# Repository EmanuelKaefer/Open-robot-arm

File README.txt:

# Robot Arm Project

This repository contains an ongoing project focused on the development of a 6-DOF robotic arm. The project is part of a school project and may later be extended into a larger final thesis project. The goal is to design and build a functional robotic arm while gaining experience in mechanical design, electronics, embedded systems, and software.

The repository includes hardware designs, firmware, control software, and documentation. As the project progresses, new features, improvements, and design iterations will be added.

# Technical Details
* Mechanical: Largely custom built. Most components are designed specifically for this project and manufactured using 3D printing.
* Electronics: Custom designed PCB created in KiCad, utilizing an STM32F446RET6 chip and TMC5160t pro 1.0 motor drivers.
* Software: Control algorithms are developed using MATLAB for modeling, simulation, and deployment.

# Licensing
This project is dual-licensed to respect the different requirements of hardware and software development:

* Software: All code within this repository is licensed under the GNU General Public License v3.0 (GPL-3.0). See `LICENSE-SOFTWARE` for details.
* Hardware: All hardware designs, including PCB layouts and mechanical CAD files, are licensed under the CERN Open Hardware Licence Version 2 (CERN-OHL-S-2.0). See `LICENSE-HARDWARE` for details.

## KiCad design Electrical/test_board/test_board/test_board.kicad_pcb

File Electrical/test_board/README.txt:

# Test Board

This board will test the motor drivers and SPI communication before actually implementing them on the driver board.

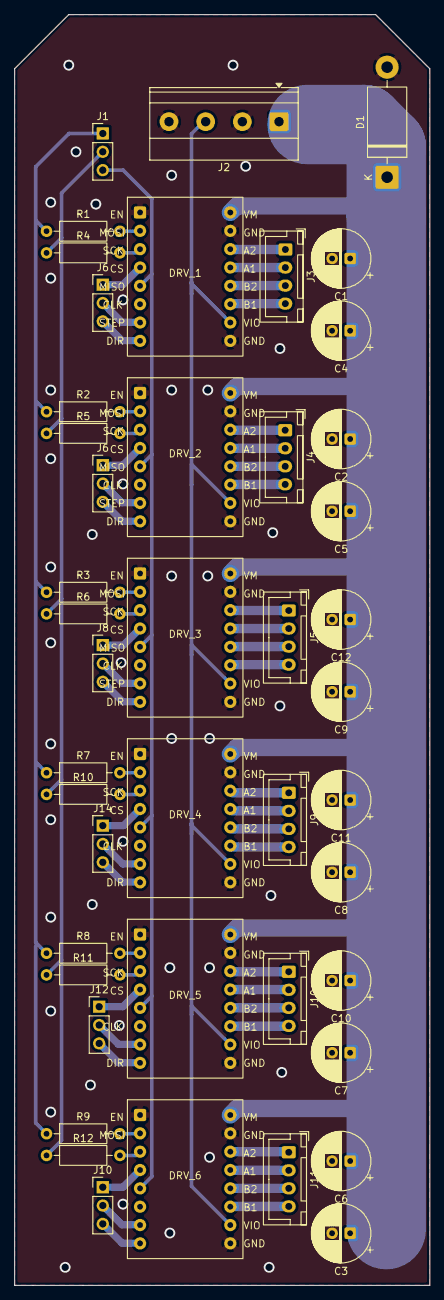
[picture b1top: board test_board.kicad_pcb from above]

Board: 2 copper layers, 57.5 x 176.0 mm, 45 parts (0 on the bottom side), 60 nets.

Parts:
C1, C2, C3, C7, C8, C9: 100nF; CP_Radial_D8.0mm_P2.50mm
C4, C5, C6, C10, C11, C12: 100uF; CP_Radial_D8.0mm_P2.50mm
D1: D_TVS; D_DO-201AD_P15.24mm_Horizontal
DRV_1, DRV_2, DRV_3, DRV_4, DRV_5, DRV_6: TMC5160T_V1.0; TMC5160T_Pro_V1.0_Breakout
J1, J6, J6#2, J8, J10, J12, J14: Conn_01x03_Pin; PinHeader_1x03_P2.54mm_Vertical
J2: Screw_Terminal_01x04; TerminalBlock_Phoenix_MKDS-1,5-4-5.08_1x04_P5.08mm_Horizont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
J3, J4, J5, J9, J10#2, J11: Conn_01x04_Socket; JST_XH_B4B-XH-A_1x04_P2.50mm_Vertical
R1, R2, R3, R4, R5, R6, R7, R8, R9, R10, R11, R12: 0Ohm; R_Axial_DIN0207_L6.3mm_D2.5mm_P10.16mm_Horizontal

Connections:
+3.3V: DRV_1.14, DRV_2.14, DRV_3.14, DRV_4.14, DRV_5.14, DRV_6.14, J2.3
+24V: C1.1, C2.1, C3.1, C4.1, C5.1, C6.1, C7.1, C8.1, C9.1, C10.1, C11.1, C12.1, D1.1 (A1), DRV_1.2, DRV_2.2, DRV_3.2, DRV_4.2, DRV_5.2, DRV_6.2, J2.1
GND: C1.2, C2.2, C3.2, C4.2, C5.2, C6.2, C7.2, C8.2, C9.2, C10.2, C11.2, C12.2, D1.2 (A2), DRV_1.1, DRV_1.4, DRV_1.16, DRV_2.1, DRV_2.4, DRV_2.16, DRV_3.1, DRV_3.4, DRV_3.16, DRV_4.1, DRV_4.4, DRV_4.16, DRV_5.1, DRV_5.4, DRV_5.16, DRV_6.1, DRV_6.4, DRV_6.16, J2.2, J2.4
MISO: DRV_1.9, DRV_2.9, DRV_3.9, DRV_4.9, DRV_5.9, DRV_6.9, J1.3
MOSI: J1.1, R1.1, R2.1, R3.1, R7.1, R8.1, R9.1
unnamed: DRV_1.3, R1.2
unnamed: DRV_1.5, R4.2
unnamed: DRV_1.6, J3.1
unnamed: DRV_1.7, J6.1
unnamed: DRV_1.8, J3.2
unnamed: DRV_1.10, J3.3
unnamed: DRV_1.12, J3.4
unnamed: DRV_1.13, J6.2
unnamed: DRV_1.15, J6.3
unnamed: DRV_2.3, R2.2
unnamed: DRV_2.5, R5.2
unnamed: DRV_2.6, J4.1
unnamed: DRV_2.7, J6#2.1
unnamed: DRV_2.8, J4.2
unnamed: DRV_2.10, J4.3
unnamed: DRV_2.12, J4.4
unnamed: DRV_2.13, J6#2.2
unnamed: DRV_2.15, J6#2.3
unnamed: DRV_3.3, R3.2
unnamed: DRV_3.5, R6.2
unnamed: DRV_3.6, J5.1
unnamed: DRV_3.7, J8.1
unnamed: DRV_3.8, J5.2
unnamed: DRV_3.10, J5.3
unnamed: DRV_3.12, J5.4
unnamed: DRV_3.13, J8.2
unnamed: DRV_3.15, J8.3
unnamed: DRV_4.3, R7.2
unnamed: DRV_4.5, R10.2
unnamed: DRV_4.6, J9.1
unnamed: DRV_4.7, J14.1
unnamed: DRV_4.8, J9.2
unnamed: DRV_4.10, J9.3
unnamed: DRV_4.12, J9.4
unnamed: DRV_4.13, J14.2
unnamed: DRV_4.15, J14.3
unnamed: DRV_5.3, R8.2
unnamed: DRV_5.5, R11.2
unnamed: DRV_5.6, J10#2.1
unnamed: DRV_5.7, J12.1
unnamed: DRV_5.8, J10#2.2
unnamed: DRV_5.10, J10#2.3
unnamed: DRV_5.12, J10#2.4
unnamed: DRV_5.13, J12.2
unnamed: DRV_5.15, J12.3
unnamed: DRV_6.3, R9.2
unnamed: DRV_6.5, R12.2
unnamed: DRV_6.6, J11.1
unnamed: DRV_6.7, J10.1
unnamed: DRV_6.8, J11.2
unnamed: DRV_6.10, J11.3
unnamed: DRV_6.12, J11.4
unnamed: DRV_6.13, J10.2
unnamed: DRV_6.15, J10.3
SCK: J1.2, R4.1, R5.1, R6.1, R10.1, R11.1, R12.1

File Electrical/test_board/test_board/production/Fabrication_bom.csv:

Designator,Footprint,Quantity,Value,LCSC Part #
"C1, C2, C3, C7, C8, C9",CP_Radial_D8.0mm_P2.50mm,6,100nF,
"C10, C11, C12, C4, C5, C6",CP_Radial_D8.0mm_P2.50mm,6,100uF,
D1,D_DO-201AD_P15.24mm_Horizontal,1,D_TVS,
"DRV_1, DRV_2, DRV_3, DRV_4, DRV_5, DRV_6",TMC5160T_Pro_V1.0_Breakout,6,TMC5160T_V1.0,
"J1, J10_2, J12, J14, J6_2, J6, J8",PinHeader_1x03_P2.54mm_Vertical,7,Conn_01x03_Pin,
"J10, J11, J3, J4, J5, J9",JST_XH_B4B-XH-A_1x04_P2.50mm_Vertical,6,Conn_01x04_Socket,
J2,"TerminalBlock_Phoenix_MKDS-1,5-4-5.08_1x04_P5.08mm_Horizontal",1,Screw_Terminal_01x04,
"R1, R10, R11, R12, R2, R3, R4, R5, R6, R7, R8, R9",R_Axial_DIN0207_L6.3mm_D2.5mm_P10.16mm_Horizontal,12,0Ohm,

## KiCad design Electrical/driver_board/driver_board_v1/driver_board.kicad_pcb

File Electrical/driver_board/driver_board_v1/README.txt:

# Motor Driver Board

This board will handle the power and control signals for the robot arm's motors.

Decisions pending:
- Supply voltage (12V/24V/etc)
- Motor driver ICs
- MCU interface logic levels
- Connector types
- Current limits

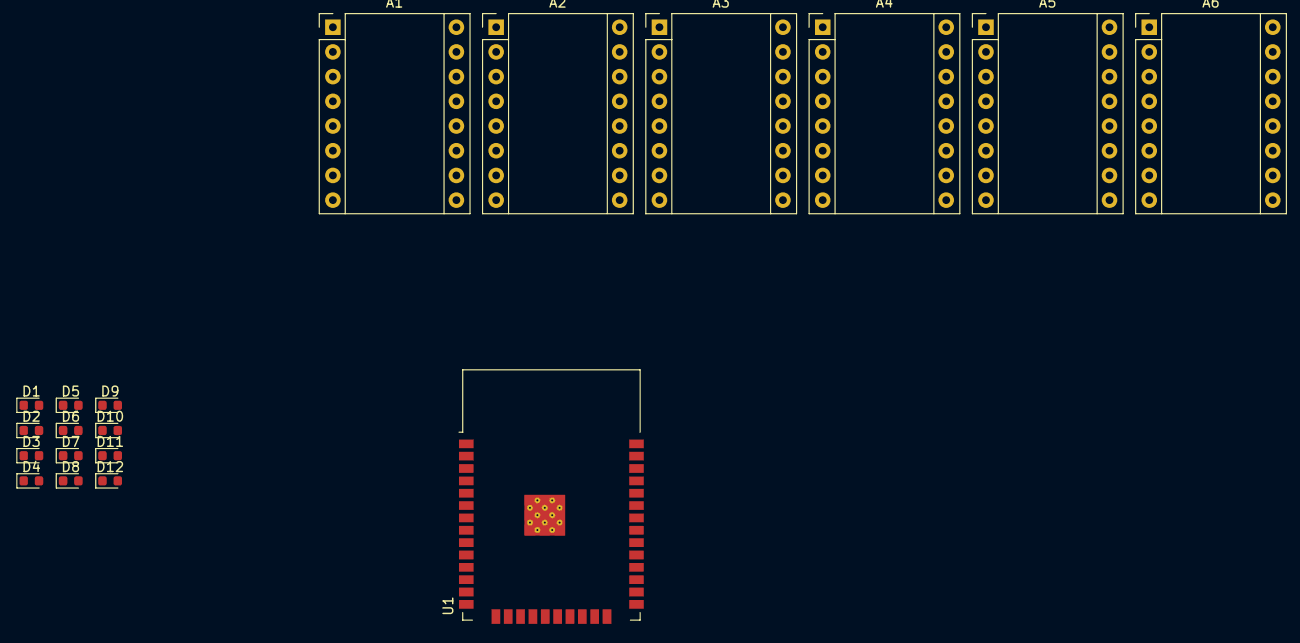
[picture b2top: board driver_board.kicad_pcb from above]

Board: 2 copper layers, 19 parts (0 on the bottom side), 26 nets, no tracks yet.

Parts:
A1, A2, A3, A4, A5, A6: Pololu_Breakout_A4988; Pololu_Breakout-16_15.2x20.3mm
D1, D2, D3, D4, D5, D6, D7, D8, D9, D10, D11, D12: LED; LED_0603_1608Metric
U1: ESP32-WROOM-32

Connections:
GND: A1.9 (~ENABLE), A2.9 (~ENABLE), A3.9 (~ENABLE), A4.9 (~ENABLE), A5.9 (~ENABLE), A6.9 (~ENABLE)
IO2: A6.13 (~RESET), U1.24 (IO2)
IO4: A5.13 (~RESET), U1.26 (IO4)
IO5: A4.13 (~RESET), U1.29 (IO5)
IO12: A3.13 (~RESET), U1.14 (IO12)
IO13: A2.13 (~RESET), U1.16 (IO13)
IO14: A1.13 (~RESET), U1.13 (IO14)
IO33: A1.10 (MS1), A2.10 (MS1), A3.10 (MS1), A4.10 (MS1), A5.10 (MS1), A6.10 (MS1)
IO34: A1.11 (MS2), A2.11 (MS2), A3.11 (MS2), A4.11 (MS2), A5.11 (MS2), A6.11 (MS2)
IO35: A1.12 (MS3), A2.12 (MS3), A3.12 (MS3), A4.12 (MS3), A5.12 (MS3), A6.12 (MS3)
NC: U1.3 (EN), U1.4 (SENSOR_VP), U1.5 (SENSOR_VN), U1.17 (SHD/SD2), U1.18 (SWP/SD3), U1.19 (SCS/CMD), U1.20 (SCK/CLK), U1.21 (SDO/SD0), U1.22 (SDI/SD1), U1.25 (IO0)
unnamed: A1.16 (DIR), D2.1 (K)
unnamed: A1.15 (STEP), D1.1 (K)
unnamed: A1.2 (VDD), A1.14 (~SLEEP), A2.2 (VDD), A2.14 (~SLEEP), A3.2 (VDD), A3.14 (~SLEEP), A4.2 (VDD), A4.14 (~SLEEP), A5.2 (VDD), A5.14 (~SLEEP), A6.2 (VDD), A6.14 (~SLEEP), U1.2 (VDD)
unnamed: A1.8 (VMOT), A2.8 (VMOT), A3.8 (VMOT), A4.8 (VMOT), A5.8 (VMOT), A6.8 (VMOT)
unnamed: A2.16 (DIR), D8.1 (K)
unnamed: A2.15 (STEP), D7.1 (K)
unnamed: A3.16 (DIR), D4.1 (K)
unnamed: A3.15 (STEP), D3.1 (K)
unnamed: A4.16 (DIR), D10.1 (K)
unnamed: A4.15 (STEP), D9.1 (K)
unnamed: A5.16 (DIR), D6.1 (K)
unnamed: A5.15 (STEP), D5.1 (K)
unnamed: A6.16 (DIR), D12.1 (K)
unnamed: A6.15 (STEP), D11.1 (K)
unnamed: A1.1 (GND), A1.7 (GND), A2.1 (GND), A2.7 (GND), A3.1 (GND), A3.7 (GND), A4.1 (GND), A4.7 (GND), A5.1 (GND), A5.7 (GND), A6.1 (GND), A6.7 (GND), U1.1 (GND), U1.15 (GND), U1.38 (GND), U1.39 (GND)

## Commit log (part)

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2025-10-09 Test
    Test
2025-10-09 Repository Structure
    Added Folders
2025-10-10 Mechanical parts prototype
    Prototype for the Arm
2025-10-11 V2 Prototype
2025-10-12 KiCad project and README for motor driver board
2025-10-12 Initial software skeleton and README for robot arm control
2025-10-12 Initial README for the project
2025-10-12 Smaller clearance
2025-10-12 added parts
2025-10-13 V3 1st joint spun by nema 17
    Base motor added spins 1st joint
2025-10-14 Driver_Board schematic changes
    Added smoothing capacitors
2025-10-14 Update to driver board v1
2025-10-14 Updated driver board v1
    New dip switch allignment and assigned first footprints
2025-10-15 V3 new design
2025-10-15 V3_3 Forearm assembly added
2025-10-17 Gearing added
2025-10-19 Cover added to oberarm
2025-10-19 small tweaks
2025-11-04 Create Endschalter1.ino
    first test code
2025-11-05 small changes
    some changes were made
2025-11-05 fore arm steuerrung mit homing funktion
2025-11-05 manual reset
    reset per vor und zurück
2025-11-06 Design changes
2025-11-06 new code + small design changes
    new code for oberarm + fore-oberarm together and small design tweaks
2025-11-07 software tweaks
2025-11-07 Base plate and gears added
2025-11-10 added new gears
2025-11-12 Updates to MCU
2025-11-13 urdf
2025-11-13 New urdf + mesh
2025-11-13 Update to mcu
2025-11-13 ros2 first prototype
2025-11-13 small tweaks in the urdf
2025-11-19 changes to make rivz worh
    Changes in the urdf and meshes to make rivz show the current arm Version
2025-11-23 V4 Robotarm design added
2025-11-24 manual controller changes
2025-11-24 mostly finished V4 arm
2025-11-25 urdf + collisions added
2025-11-25 name changes
2025-11-26 V4 base added
2025-11-26 3mfs of V4 added
2025-12-01 change of file structure
2025-12-02 gripper v1 and v2 added
2025-12-02 gripper added to robotarm
2025-12-04 Full gripper, universal gripper and urdf added
    Full gripper, universal gripper and urdf for self made gripper added
2025-12-04 removed old files
2026-01-13 Repository clean up
2026-02-02 initial commit
    adds urdf, csv, meshes and a simple Matlab script which displays the robot
2026-02-02 Update MATLAB live script show_robot.mlx
    Update the show_robot.mlx MATLAB live script used for the robot arm visualization. It now displays a few important parameters of the robot
2026-02-04 very simple algorithm ik and first simulink try
    A very simple Matbal inverse kinematics algorithm and a first simulink programm which only displays the robot
2026-02-05 Update to circuit
2026-02-05 Added pin definition
2026-02-05 first try in motion planing and ik in Simulink
    a matlab script for simple waypoint motion planing in matlab and a ik solver and simulation in simulink
2026-02-16 first try in adding pick-and-place motion planning with IK and trajectory generation
    feat: first try in adding pick-and-place motion planning with IK and trajectory generation
    - Connect Transform Trajectory to Inverse Kinematics block
    - Add Simulink-PS Converter input filtering (order 2) for smooth joint motion
    - Add Unit Delay feedback for IK initial guess continuity
    - Add model InitFcn callback to auto-load robot model
2026-02-17 add pick-and-place trajectory planning with multi-waypoint support
    Add Trapezoidal Velocity Profile Trajectory block for smooth
    multi-waypoint path generation (replaces chained Transform Trajectory)
    Tested with 4 waypoints for pick-lift-move-place cycle
    Without any gripper support yet
2026-02-19 first try in making a gripper controller
    added more waypoints for a better pick and place operation and fixed position of pick and place objekt.
    first steps in creating a gripper controller.
2026-02-26 small changes
2026-03-02 small changes and clean up
    deleted gripper controller
2026-03-04 first steps in making the simulink model ready to generate code for a microprozessor
    first steps in making the simulink model ready to generate code for a microprozessor
    removed the inverse kinematiks block in the simulink model and changed the waypoints from cartesian to joint angles
2026-03-06 Added full PSU architecture to driverboard
    +24V In
    +12V out
    +5V out
    +3.3V out
2026-03-06 Cleaned up a bit and fixed mistake with NRST pin
2026-03-24 Add TMC5160 Software SPI example
    Add an Arduino example (Software_SPI_com.ino) demonstrating communication with a TMC5160 using the TMCStepper library.
2026-03-26 Added footprint of motor driver and added power
2026-03-26 add Roboterarm project
    Update TMC SPI example and add a new PlatformIO sample project for a Roboterarm.
2026-03-26 Move Roboterarm to Robot-platformio
    Reorganize test code by renaming the Roboterarm test folder to Robot-platformio
2026-03-29 Add TMC5160A datasheet (rev 1.18)
    Add TMC5160A_datasheet_rev1.18.pdf to doc/Datasheet.r.
2026-03-31 first test with raspberry pi
    first test with raspberry pi
2026-04-01 Add TMC5160 test script for Raspberry Pi
    Add a working TMC5160 test script that uses spidev and RPi.GPIO to configure and exercise a stepper driver. The script clears latched faults, writes GCONF, IHOLD_IRUN, CHOPCONF (set for 16 microsteps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
2026-04-01 Add TMC5160 SPI setup and debug scripts
    Add two Python utilities for TMC5160 stepper driver diagnostics and configuration over SPI: setupTMC5160.py clears latched faults, programs GCONF/IHOLD_IRUN/CHOPCONF/PWMCONF and verifies driver readi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
2026-04-01 simulink file for DIR/STEP pins
    simulink file for DIR/STEP pins
2026-04-15 Refactor 6-axis stepper control to use continuous velocity (qd)
    - Eliminated initial trajectory spikes and quantization noise (staircase effect/oscillations).
    - Replaced complex Simulink blocks (1/z, round, diff) with a clean, vectorized MATLAB Function block.
    - Implemented array processing to generate absolute step frequencies (Hz) and direction signals (1/-1) for all 6 joints simultaneously.
    - Validated perfectly synchronized, smooth trapezoidal velocity profiles.
    - Prepared model architecture for open-loop hardware deployment (RasPi -> MCU -> TMC5160).
2026-04-16 small changes
    addad a new scope
2026-04-16 Add LaTeX template for documentation
    initial commit adding a LaTeX template
2026-04-16 add gitignore
2026-04-16 updated gitignore
2026-04-20 Schematic update
2026-04-21 Hierarchy changes
2026-04-21 Readme for firmware
2026-04-21 Add STM32F446RE firmware project and drivers
    Add a new STM32CubeIDE firmware project for the driver_board_v2 (target: STM32F446RETx). Includes project metadata (.ioc, .cproject, .mxproject, .project), Core sources and headers (Core/Src, Core/In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
2026-04-21 Add USART3 and stepper control helpers
    Introduce UART3 (huart3) with MX_USART3_UART_Init and enable GPIOB clock. Add stepper helper functions Step_Start, Step_Stop and Step_SetFreqHz to configure TIM1 PWM frequency and duty include bounds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
2026-04-22 restructure
2026-04-23 Added peripheral page
2026-04-23 Defined Pins
2026-04-23 Discovered critical error and changed pinout
2026-04-23 Add timers, PWM channels and TMC pin mappings
    Add TIM2/3/4/5/8/10 support and PWM channel configuration, plus pin mappings for TMC1..TMC6 (CS/STEP/DIR). Implement MX_TIM*_Init functions, register them in main, and update HAL MSP to enable clocks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
2026-04-23 Fixing bug
2026-04-23 repository bug fix
2026-04-24 docs: update READMEs to reflect project progress
    Agent-Logs-Url: https://github.com/EmanuelKaefer/Open-robot-arm/sessions/04fa266f-5e17-4764-9967-c31f6799e8a7
2026-04-27 Add SPI stubs, homing IRQs, and motor tweaks, fixed interrupt not working
    Add SPIconfig.h/.c stubs and include SPIconfig in main.h. Update main.c to add a stoprequest flag, adjust stepper behavior (start uses higher step frequency and restores holding current, stop lowers 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
2026-04-27 Add TMC SPI read/write and refactor main
    Move and implement TMC SPI register access into SPIconfig (TMC_WriteReg, TMC_ReadReg) and add prototypes to SPIconfig.h , fix minor type/format issues (limit_rad initialization, comment translations)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
2026-04-28 Add LICENSE-SOFTWARE file
2026-04-28 Add CERN Open Hardware Licence Version 2
    Added CERN Open Hardware Licence Version 2 - Strongly Reciprocal to the project.
2026-04-28 Update README with technical details and licensing
    Added technical details and licensing information for hardware and software. Added Dual license.
2026-04-28 Add homing offset handling and timer/IRQ support
    Implement precise homing offset sequence and timer/IRQ plumbing: add step-tracking globals, motor parameters and Step_Start_Exact() to run an exact number of steps while restoring TMC run current. Ad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
2026-04-29 fixing dir pin
    fixing dir pin layout so the motor changes direction
2026-04-30 copyright on Solid
2026-05-01 Add SPDX headers and tweak stepper speeds
    Insert SPDX GPL-3.0-or-later license headers and copyright notices.
    See LICENSE-SOFTWARE in the project root for full license details.
2026-05-08 Refactor homing for multi axis
    Convert homing/stepping code to support 6 axes: replace single-step counters with arrays, add AXIS_TIMERS/AXIS_CHANNELS, and change Step_Start/Stop/SetFreq/Start_Exact to accept an axis index. Add ex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
2026-05-08 Scale TMC SPI functions for more axis
    Update SPI/TMC interfaces to support multiple axes by adding an axis parameter . Also include an updated documentation ODT
2026-05-10 Update documentation
2026-05-11 small changes in the solid
2026-05-11 Robotarm V5
    In V5 there are new bearing with other dimensions
2026-05-12 Added small test board
2026-05-12 Some tweaks on V5 assembly
    changed some dimensions in v5 an added some main parts to print
2026-05-12 Made and added footprint for tmc5160t pro v1.0
2026-05-12 Updated test board
2026-05-13 fixed severe issue in test board
2026-05-16 Updated testboard
2026-05-18 Upgrade to testboard
2026-05-18 Finished testboard
2026-05-18 Added README for testboard
2026-05-18 Cleaned up test board
2026-05-18 Adjusted test board
2026-05-19 improvement
2026-05-19 testboard revision
2026-05-19 Improve homing, add URDF tool and update docs
    Firmware: adjust homing parameters and add debug prints in main.c — home_rad set to zeros because of defined homeposition in the urdf, limit_rad corrected, and several printf() calls added for tracin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
2026-05-27 Update Documentation
    Expand and restructure the software chapter
2026-05-28 V6 folder structur created
2026-05-28 Fixed the whole test thing
2026-05-28 Update software chapter: low-level arch & homing
    Revise Software chapter
2026-05-28 update doc
    update Software doc
2026-05-29 Final adjustments to test board (hopefully)
2026-06-01 Optical adjustments
2026-06-01 add docs
    update template documentation files and (tex/aux/pdf/figures) including SPIMode.png.
2026-06-02 Small changes to routes
2026-06-03 update doc
    update software part in doc
2026-06-04 remove old files
    remove all old files that are not important anymore
2026-06-04 ik code to run on the raspberry pi
    ik code to run on the raspberry pi, changed necessary things in urdf: remove mesh references, j1, j4, j6 from continiout to limits
2026-06-07 updated doc
    updated Software doc
2026-06-09 update doc
    update electrik doc
2026-06-09 gitignore
2026-06-11 replacing endstops with encoder
    replacing endstops with encoder: delete alle interrupt/endstop related stuff and add encoderpins and the code for encoder with DMA
2026-06-12 Changed switches to encoder
2026-06-19 update doc
    update doc
2026-06-19 update doc
    finish the doc for ASIT
2026-06-23 define pin PB9 for gripper servo
    define pin PB9 for gripper servo
2026-06-23 Added gripper
2026-06-23 Added TMC and MCU Labeling
2026-06-23 Finished TMC Labeling
